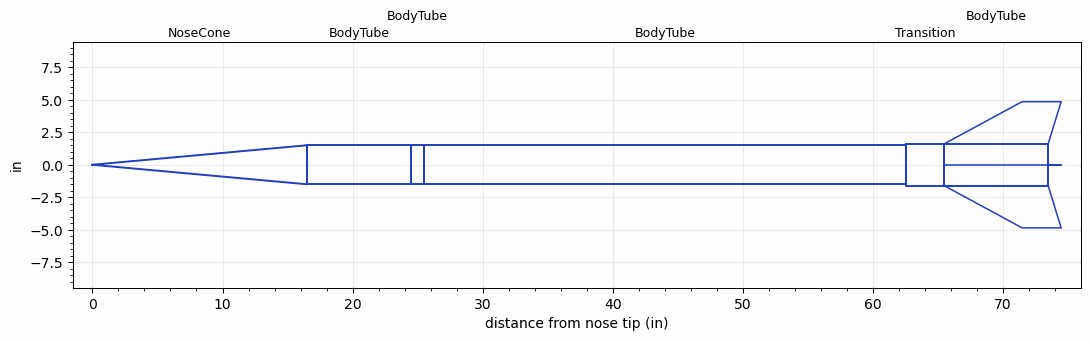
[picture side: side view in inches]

<RASAeroDocument>
 <FileVersion>2</FileVersion>
 <RocketDesign>
  <NoseCone>
   <Length>16.5</Length>
   <Diameter>3</Diameter>
   <Shape>Conical</Shape>
   <BluntRadius>0.065</BluntRadius>
   <Location>0</Location>
  </NoseCone>
  <BodyTube>
   <Length>8</Length>
   <Diameter>3</Diameter>
   <Location>16.5</Location>
  </BodyTube>
  <BodyTube>
   <Length>1</Length>
   <Diameter>3</Diameter>
   <Location>24.5</Location>
  </BodyTube>
  <BodyTube>
   <Length>36.9999</Length>
   <Diameter>3</Diameter>
   <Location>25.5</Location>
  </BodyTube>
  <Transition>
   <Length>2.9528</Length>
   <Diameter>3.2</Diameter>
   <Location>62.4999</Location>
   <RearDiameter>3.2</RearDiameter>
  </Transition>
  <BodyTube>
   <Length>8</Length>
   <Diameter>3.2</Diameter>
   <Location>65.4527</Location>
   <Fin>
    <Count>4</Count>
    <Chord>8</Chord>
    <Span>3.25</Span>
    <SweepDistance>6</SweepDistance>
    <TipChord>3</TipChord>
    <Thickness>0.1875</Thickness>
    <LERadius>0.02</LERadius>
    <Location>8</Location>
    <AirfoilSection>Hexagonal</AirfoilSection>
    <FX1>0.75</FX1>
    <FX3>0.75</FX3>
   </Fin>
  </BodyTube>
  <Surface>Rough Camouflage Paint</Surface>
  <ModifiedBarrowman>True</ModifiedBarrowman>
  <Turbulence>True</Turbulence>
  <UseBooster1>False</UseBooster1>
  <UseBooster2>False</UseBooster2>
 </RocketDesign>
 <LaunchSite>
  <Altitude>2500</Altitude>
  <Pressure>29.92</Pressure>
  <RodAngle>3</RodAngle>
  <RodLength>10</RodLength>
  <Temperature>40</Temperature>
  <WindSpeed>4.47</WindSpeed>
 </LaunchSite>
 <Recovery>
  <Altitude1>1000</Altitude1>
  <Altitude2>0</Altitude2>
  <DeviceType1>Parachute</DeviceType1>
  <DeviceType2>None</DeviceType2>
  <Event1>True</Event1>
  <Event2>False</Event2>
  <Size1>39.9999</Size1>
  <Size2>0</Size2>
  <EventType1>Altitude</EventType1>
  <EventType2>None</EventType2>
  <CD1>0.8</CD1>
  <CD2>0</CD2>
 </Recovery>
 <SimulationList>
  <Simulation>
   <SustainerEngine>M2700W-PS  (AT)</SustainerEngine>
   <SustainerLaunchWt>22.7</SustainerLaunchWt>
   <SustainerNozzleDiameter>3</SustainerNozzleDiameter>
   <SustainerCG>46.92</SustainerCG>
   <SustainerIgnitionDelay>0</SustainerIgnitionDelay>
   <Booster1SeparationDelay>0</Booster1SeparationDelay>
   <Booster1IgnitionDelay>0</Booster1IgnitionDelay>
   <IncludeBooster1>False</IncludeBooster1>
   <Booster2Delay>0</Booster2Delay>
   <IncludeBooster2>False</IncludeBooster2>
   <TimetoApogee>40.67918</TimetoApogee>
   <MaxAltitude>42238.34</MaxAltitude>
   <MaxVelocity>3746.457</MaxVelocity>
  </Simulation>
 </SimulationList>
</RASAeroDocument>
